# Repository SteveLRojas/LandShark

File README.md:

# LandShark
FPGA board for motor control applications. Compatible with the Alchemy board.

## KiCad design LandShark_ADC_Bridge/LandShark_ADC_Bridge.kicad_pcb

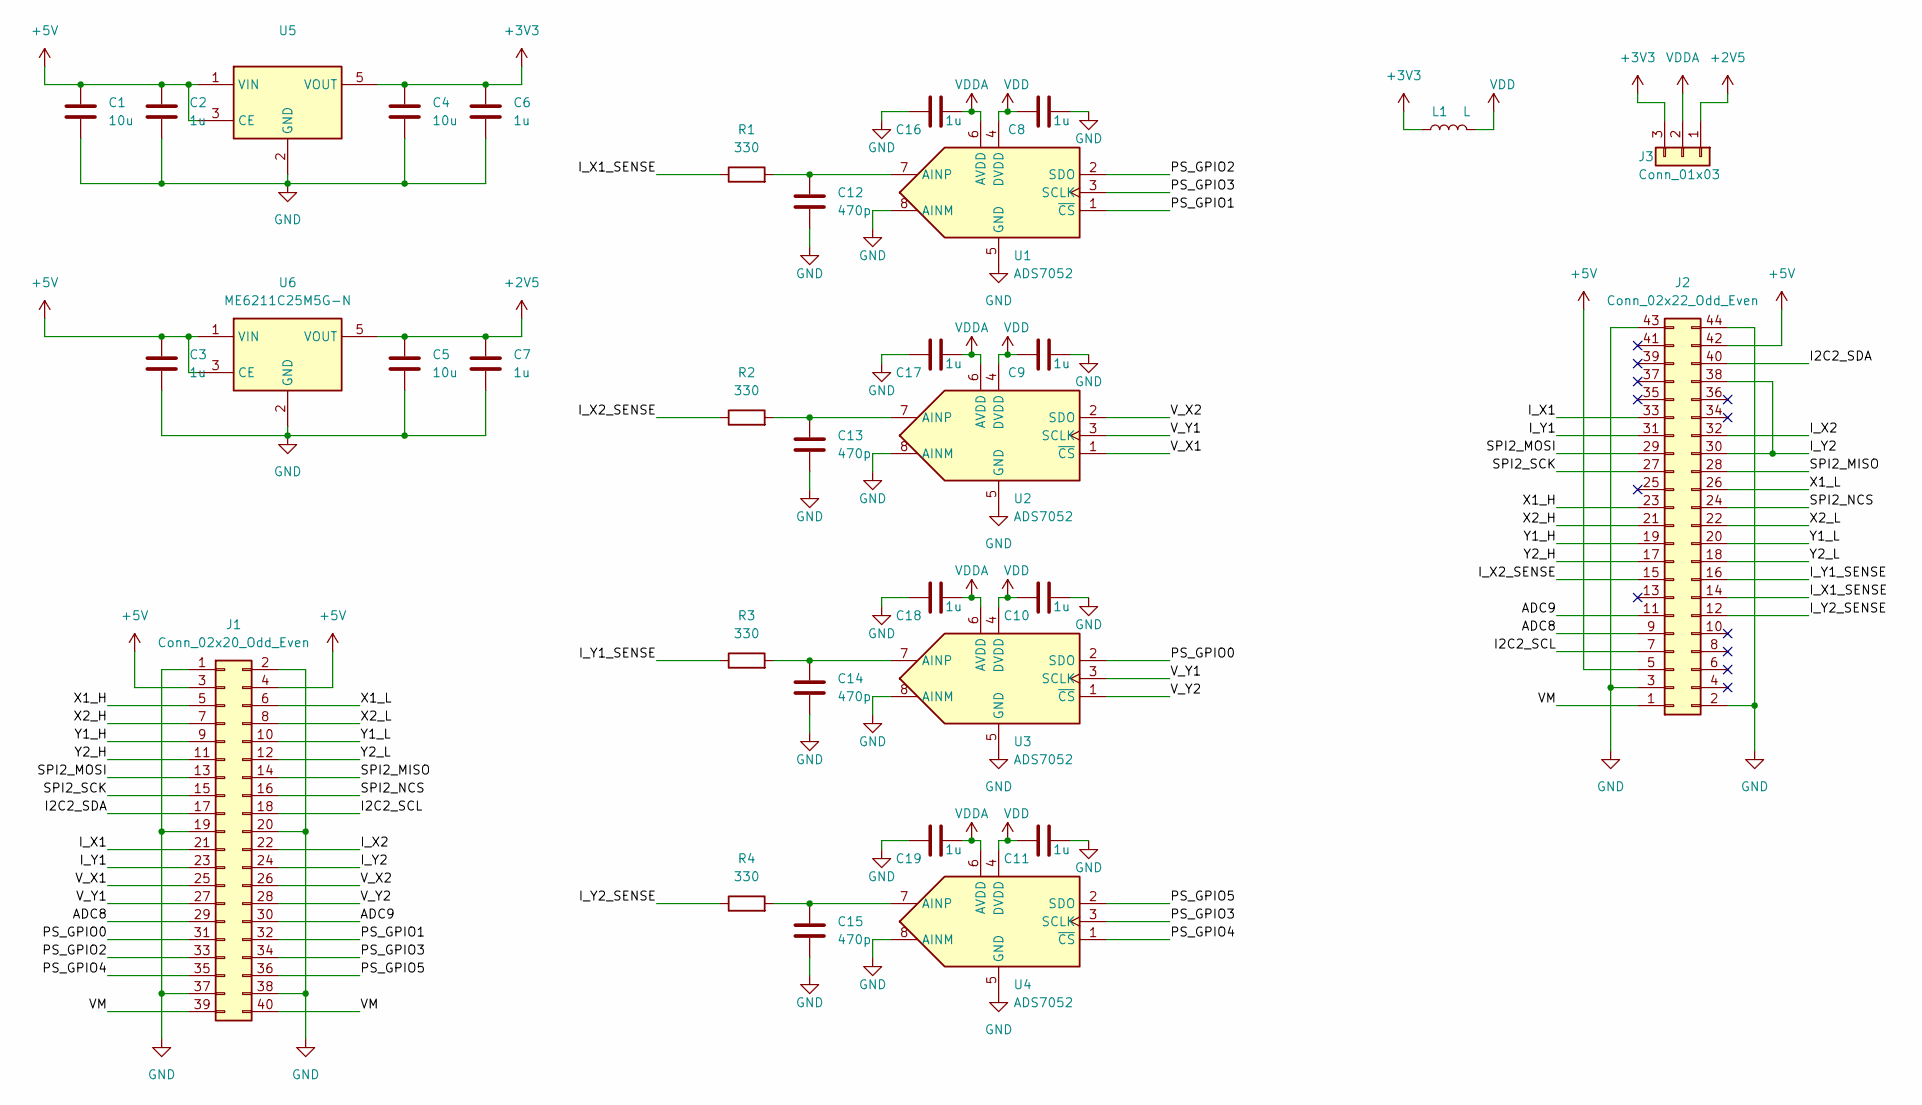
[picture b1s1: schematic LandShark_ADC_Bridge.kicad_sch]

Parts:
C1, C4, C5: 10u; C_1206_3216Metric
C2, C3, C6, C7, C8, C9, C10, C11, C16, C17, C18, C19: 1u; C_0805_2012Metric
C12, C13, C14, C15: 470p; C_0603_1608Metric
J1: Conn_02x20_Odd_Even; con_Alchemy_mirrored
J2: Conn_02x22_Odd_Even; PinHeader_2x22_P2.54mm_Vertical
J3: Conn_01x03; PinHeader_1x03_P1.27mm_Vertical
L1: L; L_0805_2012Metric
R1, R2, R3, R4: 330; R_0603_1608Metric
U1, U2, U3, U4: ADS7052; ADS7052IRUGR
U5: XC6219B332MR; SOT-23-5
U6: ME6211C25M5G-N; SOT-23-5

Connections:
+2V5: C5.1, C7.1, J3.1, U6.5 (VOUT)
+3V3: C4.1, C6.1, J3.3, L1.1, U5.5 (VOUT)
+5V: C1.1, C2.1, C3.1, J1.3, J1.4, J2.5, J2.42, U5.1 (VIN), U5.3 (CE), U6.1 (VIN), U6.3 (CE)
/ADC8: J1.29, J2.9
/ADC9: J1.30, J2.11
/I2C2_SCL: J1.18, J2.7
/I2C2_SDA: J1.17, J2.40
/I_X1: J1.21, J2.33
/I_X1_SENSE: J2.14, R1.1
/I_X2: J1.22, J2.32
/I_X2_SENSE: J2.15, R2.1
/I_Y1: J1.23, J2.31
/I_Y1_SENSE: J2.16, R3.1
/I_Y2: J1.24, J2.30, J2.38
/I_Y2_SENSE: J2.12, R4.1
/PS_GPIO0: J1.31, U3.2 (SDO)
/PS_GPIO1: J1.32, U1.1 (~CS)
/PS_GPIO2: J1.33, U1.2 (SDO)
/PS_GPIO3: J1.34, U1.3 (SCLK), U4.3 (SCLK)
/PS_GPIO4: J1.35, U4.1 (~CS)
/PS_GPIO5: J1.36, U4.2 (SDO)
/SPI2_MISO: J1.14, J2.28
/SPI2_MOSI: J1.13, J2.29
/SPI2_NCS: J1.16, J2.24
/SPI2_SCK: J1.15, J2.27
/VM: J1.39, J1.40, J2.1
/V_X1: J1.25, U2.1 (~CS)
/V_X2: J1.26, U2.2 (SDO)
/V_Y1: J1.27, U2.3 (SCLK), U3.3 (SCLK)
/V_Y2: J1.28, U3.1 (~CS)
/X1_H: J1.5, J2.23
/X1_L: J1.6, J2.26
/X2_H: J1.7, J2.21
/X2_L: J1.8, J2.22
/Y1_H: J1.9, J2.19
/Y1_L: J1.10, J2.20
/Y2_H: J1.11, J2.17
/Y2_L: J1.12, J2.18
GND: C1.2, C2.2, C3.2, C4.2, C5.2, C6.2, C7.2, C8.2, C9.2, C10.2, C11.2, C12.1, C13.1, C14.1, C15.1, C16.1, C17.1, C18.1, C19.1, J1.1, J1.2, J1.19, J1.20, J1.37, J1.38, J2.2, J2.3, J2.43, J2.44, U1.5 (GND), U1.8 (AINM), U2.5 (GND), U2.8 (AINM), U3.5 (GND), U3.8 (AINM), U4.5 (GND), U4.8 (AINM), U5.2 (GND), U6.2 (GND)
unnamed: C12.2, R1.2, U1.7 (AINP)
unnamed: C13.2, R2.2, U2.7 (AINP)
unnamed: C14.2, R3.2, U3.7 (AINP)
unnamed: C15.2, R4.2, U4.7 (AINP)
VDD: C8.1, C9.1, C10.1, C11.1, L1.2, U1.4 (DVDD), U2.4 (DVDD), U3.4 (DVDD), U4.4 (DVDD)
VDDA: C16.2, C17.2, C18.2, C19.2, J3.2, U1.6 (AVDD), U2.6 (AVDD), U3.6 (AVDD), U4.6 (AVDD)

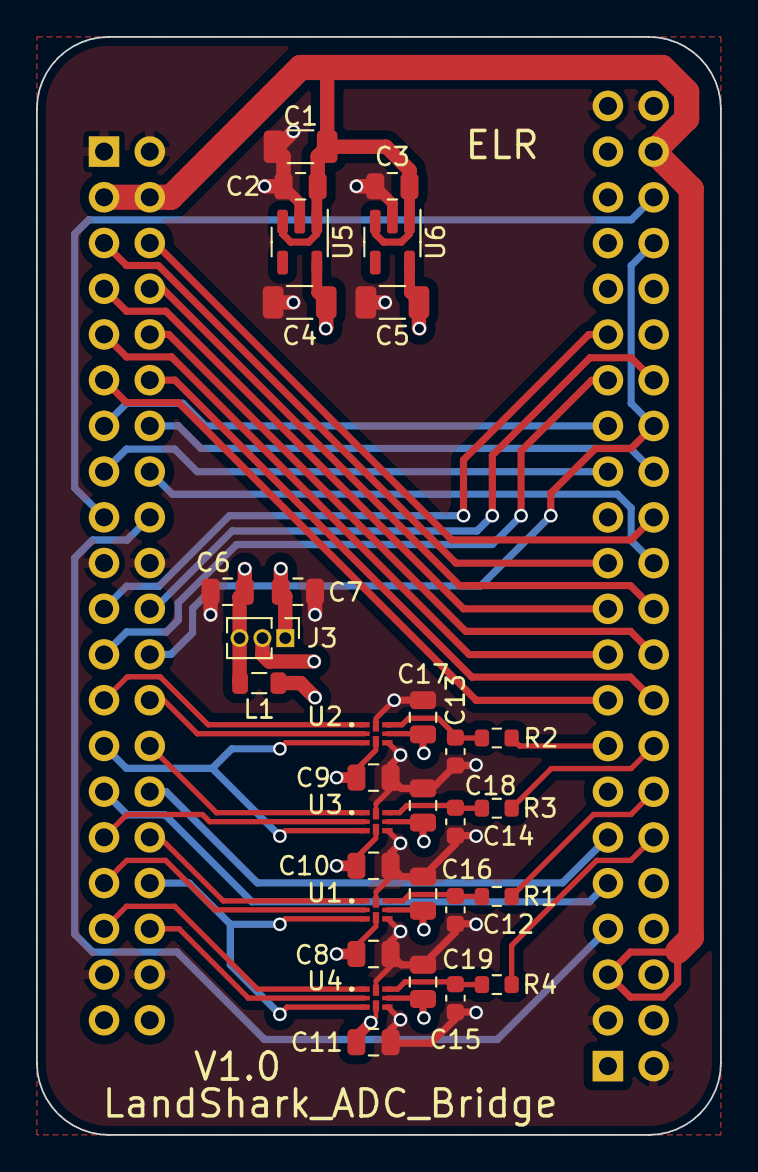
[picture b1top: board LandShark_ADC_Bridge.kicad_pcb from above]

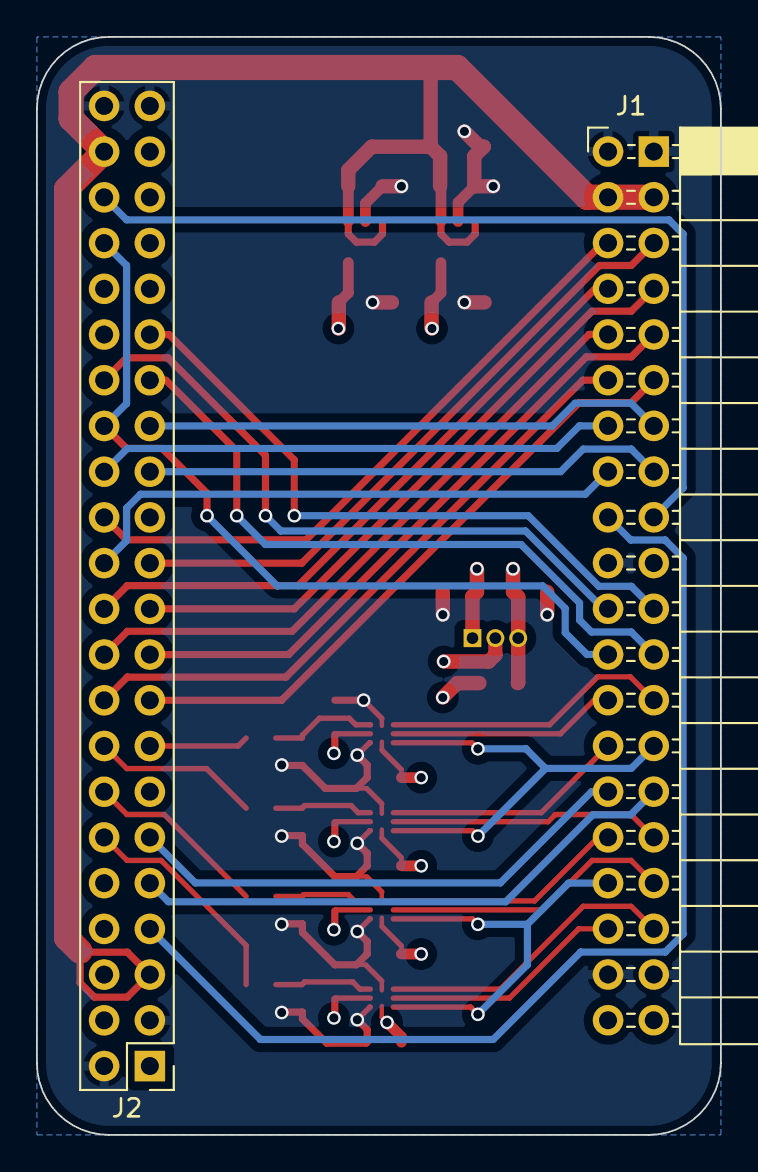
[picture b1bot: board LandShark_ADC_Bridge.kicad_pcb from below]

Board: 4 copper layers, 38.0 x 61.0 mm, 33 parts (2 on the bottom side), 45 nets.

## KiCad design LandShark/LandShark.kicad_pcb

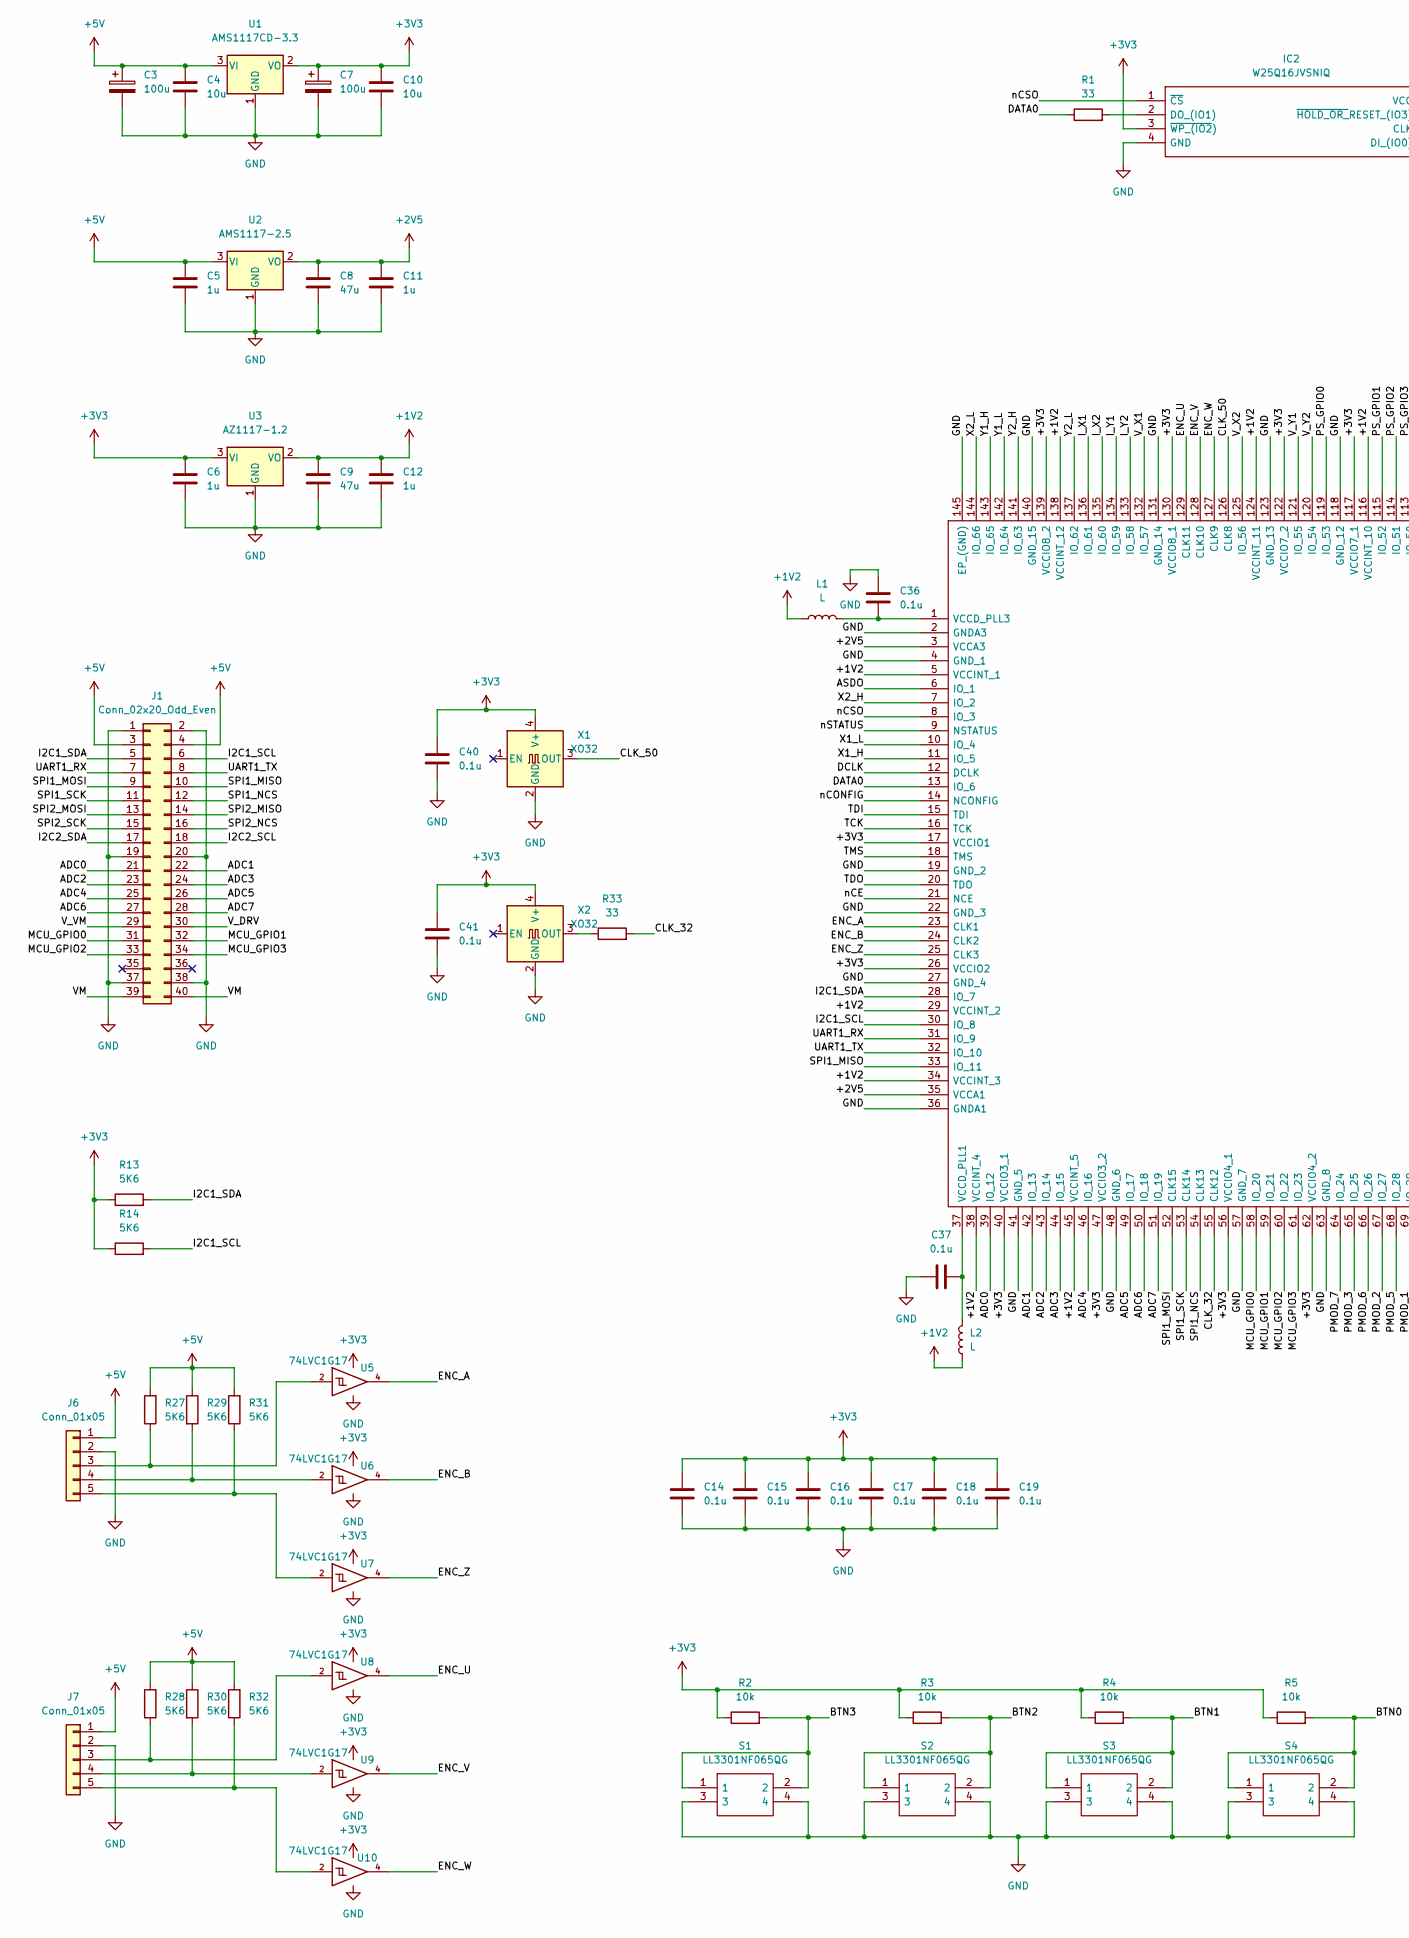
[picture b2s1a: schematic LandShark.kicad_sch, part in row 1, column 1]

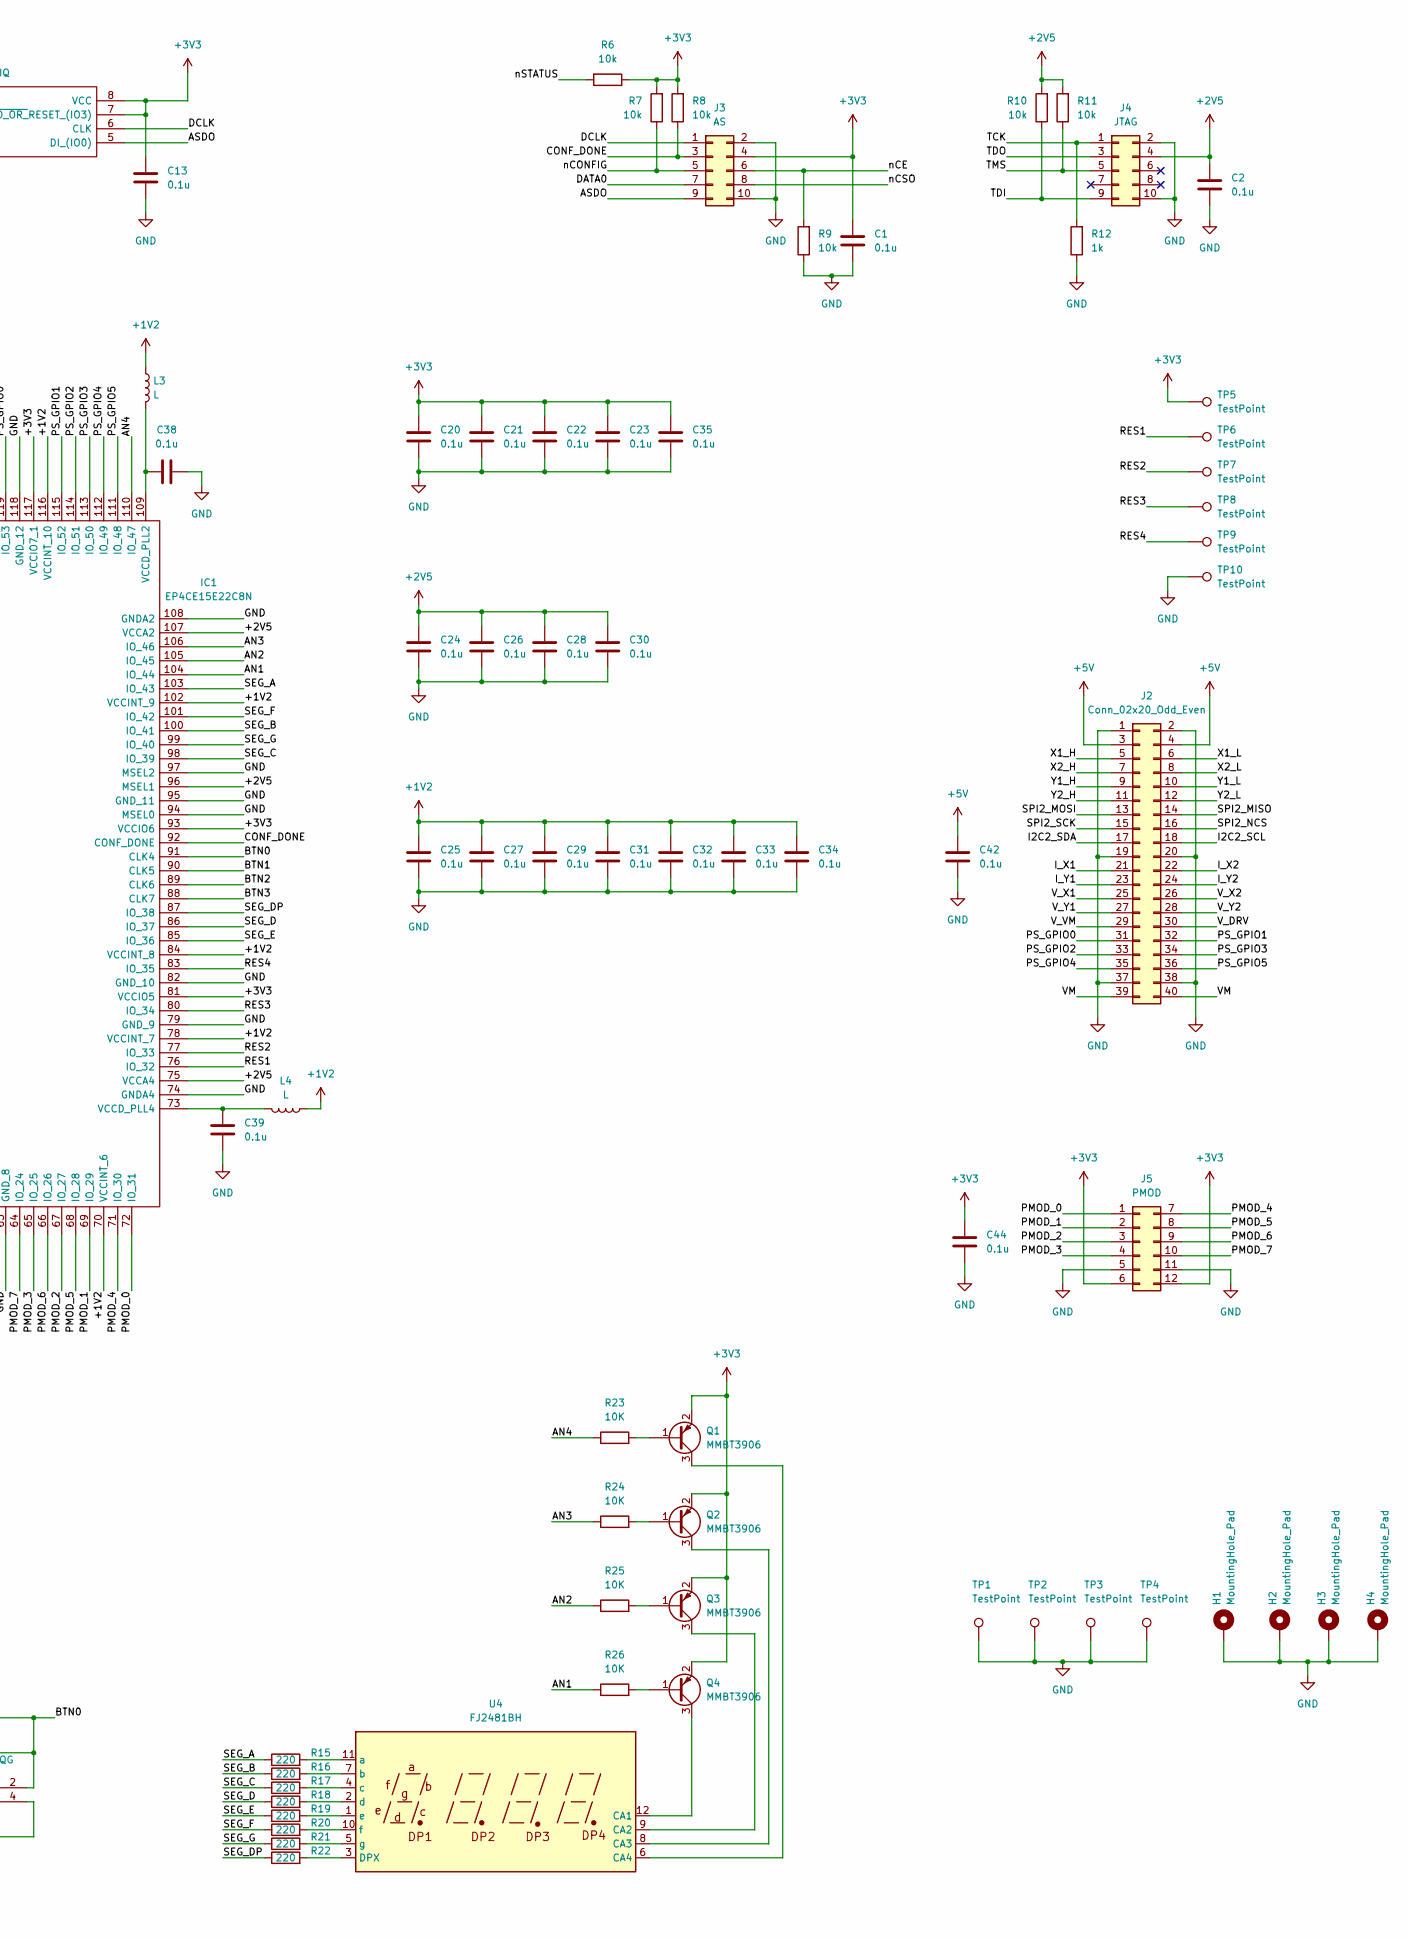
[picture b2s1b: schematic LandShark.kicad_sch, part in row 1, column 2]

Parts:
C1, C2, C13, C14, C15, C16, C17, C18, C19, C20, C21, C22, C23, C24, C25, C26, C27, C28, C29, C30, C31, C32, C33, C34, C35, C36, C37, C38, C39, C40, C41, C42, C44: 0.1u; C_0805_2012Metric
C3, C7: 100u; CP_Elec_6.3x5.2
C4, C10: 10u; C_1206_3216Metric
C5, C6, C11, C12: 1u; C_0805_2012Metric
C8, C9: 47u; C_1206_3216Metric
H1, H2, H3, H4: MountingHole_Pad; MountingHole_3.2mm_M3_Pad
IC1: EP4CE15E22C8N; QFP50P2200X2200X165-145N; Mouser Part Number 989-EP4CE15E22C8N
IC2: W25Q16JVSNIQ; SOIC127P600X175-8N; Manufacturer_Part_Number W25Q16JVSNIQ; Mouser Part Number 454-W25Q16JVSNIQ
J1: Conn_02x20_Odd_Even; PinSocket_2x20_P2.54mm_Horizontal
J2: Conn_02x20_Odd_Even; PinHeader_2x20_P2.54mm_Horizontal
J3: AS; IDC-Header_2x05_P2.54mm_Vertical
J4: JTAG; IDC-Header_2x05_P2.54mm_Vertical
J5: PMOD; pmod_socket_6x2
J6, J7: Conn_01x05; PinHeader_1x05_P2.54mm_Vertical
L1, L2, L3, L4: L; L_0805_2012Metric
Q1, Q2, Q3, Q4: MMBT3906; SOT-23
R1, R33: 33; R_0805_2012Metric
R2, R3, R4, R5, R6, R7, R8, R9, R10, R11: 10k; R_0805_2012Metric
R12: 1k; R_0805_2012Metric
R13, R14, R27, R28, R29, R30, R31, R32: 5K6; R_0805_2012Metric
R15, R16, R17, R18, R19, R20, R21, R22: 220; R_0805_2012Metric
R23, R24, R25, R26: 10K; R_0805_2012Metric
S1, S2, S3, S4: LL3301NF065QG; Mouser Part Number 612-LL3301NF065QG
TP1, TP2, TP3, TP4: TestPoint; TestPoint_Loop_D2.50mm_Drill1.0mm
TP5, TP6, TP7, TP8, TP9, TP10: TestPoint; TestPoint_Pad_1.5x1.5mm
U1: AMS1117CD-3.3; TO-252-3_TabPin2
U2: AMS1117-2.5; SOT-223-3_TabPin2
U3: AZ1117-1.2; SOT-223-3_TabPin2
U4: FJ2481BH
U5, U6, U7, U8, U9, U10: 74LVC1G17; SOT-353_SC-70-5
X1, X2: XO32; Oscillator_SMD_EuroQuartz_XO32-4Pin_3.2x2.5mm

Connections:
+1V2: C9.1, C12.1, C25.1, C27.1, C29.1, C31.1, C32.1, C33.1, C34.1, IC1.5 (VCCINT_1), IC1.29 (VCCINT_2), IC1.34 (VCCINT_3), IC1.38 (VCCINT_4), IC1.45 (VCCINT_5), IC1.70 (VCCINT_6), IC1.78 (VCCINT_7), IC1.84 (VCCINT_8), IC1.102 (VCCINT_9), IC1.116 (VCCINT_10), IC1.124 (VCCINT_11), IC1.138 (VCCINT_12), L1.1, L2.1, L3.1, L4.1, U3.2 (VO)
+2V5: C2.1, C8.1, C11.1, C24.1, C26.1, C28.1, C30.1, IC1.3 (VCCA3), IC1.35 (VCCA1), IC1.75 (VCCA4), IC1.96 (MSEL1), IC1.107 (VCCA2), J4.4, R10.2, R11.2, U2.2 (VO)
+3V3: C1.1, C6.1, C7.1, C10.1, C13.1, C14.1, C15.1, C16.1, C17.1, C18.1, C19.1, C20.1, C21.1, C22.1, C23.1, C35.1, C40.1, C41.1, C44.1, IC1.17 (VCCIO1), IC1.26 (VCCIO2), IC1.40 (VCCIO3_1), IC1.47 (VCCIO3_2), IC1.56 (VCCIO4_1), IC1.62 (VCCIO4_2), IC1.81 (VCCIO5), IC1.93 (VCCIO6), IC1.117 (VCCIO7_1), IC1.122 (VCCIO7_2), IC1.130 (VCCIO8_1), IC1.139 (VCCIO8_2), IC2.3 (~WP_(IO2)), IC2.7 (~HOLD_OR_RESET_(IO3)), IC2.8 (VCC), J3.4, J5.6, J5.12, Q1.2 (E), Q2.2 (E), Q3.2 (E), Q4.2 (E), R2.1, R3.1, R4.1, R5.1, R6.1, R7.2, R8.2, R13.1, R14.1, TP5.1, U1.2 (VO), U3.3 (VI), U5.5 (VCC), U6.5 (VCC), U7.5 (VCC), U8.5 (VCC), U9.5 (VCC), U10.5 (VCC), X1.4 (V+), X2.4 (V+)
+5V: C3.1, C4.1, C5.1, C42.1, J1.3, J1.4, J2.3, J2.4, J6.1, J7.1, R27.2, R28.2, R29.1, R30.1, R31.2, R32.2, U1.3 (VI), U2.3 (VI)
/ADC0: IC1.39 (IO_12), J1.21
/ADC1: IC1.42 (IO_13), J1.22
/ADC2: IC1.43 (IO_14), J1.23
/ADC3: IC1.44 (IO_15), J1.24
/ADC4: IC1.46 (IO_16), J1.25
/ADC5: IC1.49 (IO_17), J1.26
/ADC6: IC1.50 (IO_18), J1.27
/ADC7: IC1.51 (IO_19), J1.28
/AN1: IC1.104 (IO_44), R26.1
/AN2: IC1.105 (IO_45), R25.1
/AN3: IC1.106 (IO_46), R24.1
/AN4: IC1.110 (IO_47), R23.1
/ASDO: IC1.6 (IO_1), IC2.5 (DI_(IO0)), J3.9
/BTN0: IC1.91 (CLK4), R5.2, S4.1, S4.2
/BTN1: IC1.90 (CLK5), R4.2, S3.1, S3.2
/BTN2: IC1.89 (CLK6), R3.2, S2.1, S2.2
/BTN3: IC1.88 (CLK7), R2.2, S1.1, S1.2
/CLK_32: IC1.55 (CLK12), R33.2
/CLK_50: IC1.126 (CLK8), X1.3 (OUT)
/CONF_DONE: IC1.92 (CONF_DONE), J3.3, R8.1
/DATA0: IC1.13 (IO_6), J3.7, R1.1
/DCLK: IC1.12 (DCLK), IC2.6 (CLK), J3.1
/ENC_A: IC1.23 (CLK1), U5.4
/ENC_B: IC1.24 (CLK2), U6.4
/ENC_U: IC1.129 (CLK11), U8.4
/ENC_V: IC1.128 (CLK10), U9.4
/ENC_W: IC1.127 (CLK9), U10.4
/ENC_Z: IC1.25 (CLK3), U7.4
/I2C1_SCL: IC1.30 (IO_8), J1.6, R14.2
/I2C1_SDA: IC1.28 (IO_7), J1.5, R13.2
/I2C2_SCL: J1.18, J2.18
/I2C2_SDA: J1.17, J2.17
/I_X1: IC1.136 (IO_61), J2.21
/I_X2: IC1.135 (IO_60), J2.22
/I_Y1: IC1.134 (IO_59), J2.23
/I_Y2: IC1.133 (IO_58), J2.24
/MCU_GPIO0: IC1.58 (IO_20), J1.31
/MCU_GPIO1: IC1.59 (IO_21), J1.32
/MCU_GPIO2: IC1.60 (IO_22), J1.33
/MCU_GPIO3: IC1.61 (IO_23), J1.34
/PMOD_0: IC1.72 (IO_31), J5.1
/PMOD_1: IC1.69 (IO_29), J5.2
/PMOD_2: IC1.67 (IO_27), J5.3
/PMOD_3: IC1.65 (IO_25), J5.4
/PMOD_4: IC1.71 (IO_30), J5.7
/PMOD_5: IC1.68 (IO_28), J5.8
/PMOD_6: IC1.66 (IO_26), J5.9
/PMOD_7: IC1.64 (IO_24), J5.10
/PS_GPIO0: IC1.119 (IO_53), J2.31
/PS_GPIO1: IC1.115 (IO_52), J2.32
/PS_GPIO2: IC1.114 (IO_51), J2.33
/PS_GPIO3: IC1.113 (IO_50), J2.34
/PS_GPIO4: IC1.112 (IO_49), J2.35
/PS_GPIO5: IC1.111 (IO_48), J2.36
/RES1: IC1.76 (IO_32), TP6.1
/RES2: IC1.77 (IO_33), TP7.1
/RES3: IC1.80 (IO_34), TP8.1
/RES4: IC1.83 (IO_35), TP9.1
/SEG_A: IC1.103 (IO_43), R15.1
/SEG_B: IC1.100 (IO_41), R16.1
/SEG_C: IC1.98 (IO_39), R17.1
/SEG_D: IC1.86 (IO_37), R18.1
/SEG_DP: IC1.87 (IO_38), R22.1
/SEG_E: IC1.85 (IO_36), R19.1
/SEG_F: IC1.101 (IO_42), R20.1
/SEG_G: IC1.99 (IO_40), R21.1
/SPI1_MISO: IC1.33 (IO_11), J1.10
/SPI1_MOSI: IC1.52 (CLK15), J1.9
/SPI1_NCS: IC1.54 (CLK13), J1.12
/SPI1_SCK: IC1.53 (CLK14), J1.11
/SPI2_MISO: J1.14, J2.14
/SPI2_MOSI: J1.13, J2.13
/SPI2_NCS: J1.16, J2.16
/SPI2_SCK: J1.15, J2.15
/TCK: IC1.16 (TCK), J4.1, R12.2
/TDI: IC1.15 (TDI), J4.9, R10.1
/TDO: IC1.20 (TDO), J4.3
/TMS: IC1.18 (TMS), J4.5, R11.1
/UART1_RX: IC1.31 (IO_9), J1.7
/UART1_TX: IC1.32 (IO_10), J1.8
/VM: J1.39, J1.40, J2.39, J2.40
/V_DRV: J1.30, J2.30
/V_VM: J1.29, J2.29
/V_X1: IC1.132 (IO_57), J2.25
/V_X2: IC1.125 (IO_56), J2.26
/V_Y1: IC1.121 (IO_55), J2.27
/V_Y2: IC1.120 (IO_54), J2.28
/X1_H: IC1.11 (IO_5), J2.5
/X1_L: IC1.10 (IO_4), J2.6
/X2_H: IC1.7 (IO_2), J2.7
/X2_L: IC1.144 (IO_66), J2.8
/Y1_H: IC1.143 (IO_65), J2.9
/Y1_L: IC1.142 (IO_64), J2.10
/Y2_H: IC1.141 (IO_63), J2.11
/Y2_L: IC1.137 (IO_62), J2.12
/nCE: IC1.21 (NCE), J3.6, R9.2
/nCONFIG: IC1.14 (NCONFIG), J3.5, R7.1
/nCSO: IC1.8 (IO_3), IC2.1 (~CS), J3.8
/nSTATUS: IC1.9 (NSTATUS), R6.2
GND: C1.2, C2.2, C3.2, C4.2, C5.2, C6.2, C7.2, C8.2, C9.2, C10.2, C11.2, C12.2, C13.2, C14.2, C15.2, C16.2, C17.2, C18.2, C19.2, C20.2, C21.2, C22.2, C23.2, C24.2, C25.2, C26.2, C27.2, C28.2, C29.2, C30.2, C31.2, C32.2, C33.2, C34.2, C35.2, C36.2, C37.2, C38.2, C39.1, C40.2, C41.2, C42.2, C44.2, H1.1, H2.1, H3.1, H4.1, IC1.2 (GNDA3), IC1.4 (GND_1), IC1.19 (GND_2), IC1.22 (GND_3), IC1.27 (GND_4), IC1.36 (GNDA1), IC1.41 (GND_5), IC1.48 (GND_6), IC1.57 (GND_7), IC1.63 (GND_8), IC1.74 (GNDA4), IC1.79 (GND_9), IC1.82 (GND_10), IC1.94 (MSEL0), IC1.95 (GND_11), IC1.97 (MSEL2), IC1.108 (GNDA2), IC1.118 (GND_12), IC1.123 (GND_13), IC1.131 (GND_14), IC1.140 (GND_15), IC1.145 (EP_(GND)), IC2.4 (GND), J1.1, J1.2, J1.19, J1.20, J1.37, J1.38, J2.1, J2.2, J2.19, J2.20, J2.37, J2.38, J3.2, J3.10, J4.2, J4.10, J5.5, J5.11, J6.2, J7.2, R9.1, R12.1, S1.3, S1.4, S2.3, S2.4, S3.3, S3.4, S4.3, S4.4, TP1.1, TP2.1, TP3.1, TP4.1, TP10.1, U1.1 (GND), U2.1 (GND), U3.1 (GND), U5.3 (GND), U6.3 (GND), U7.3 (GND), U8.3 (GND), U9.3 (GND), U10.3 (GND), X1.2 (GND), X2.2 (GND)
unnamed: C36.1, IC1.1 (VCCD_PLL3), L1.2
unnamed: C37.1, IC1.37 (VCCD_PLL1), L2.2
unnamed: C39.2, IC1.73 (VCCD_PLL4), L4.2
unnamed: C38.1, IC1.109 (VCCD_PLL2), L3.2
unnamed: IC2.2 (DO_(IO1)), R1.2
unnamed: J6.3, R27.1, U5.2
unnamed: J6.4, R29.2, U6.2
unnamed: J6.5, R31.1, U7.2
unnamed: J7.3, R28.1, U8.2
unnamed: J7.4, R30.2, U9.2
unnamed: J7.5, R32.1, U10.2
unnamed: Q1.1 (B), R23.2
unnamed: Q1.3 (C), U4.6 (CA4)
unnamed: Q2.1 (B), R24.2
unnamed: Q2.3 (C), U4.8 (CA3)
unnamed: Q3.1 (B), R25.2
unnamed: Q3.3 (C), U4.9 (CA2)
unnamed: Q4.1 (B), R26.2
unnamed: Q4.3 (C), U4.12 (CA1)
unnamed: R15.2, U4.11 (a)
unnamed: R16.2, U4.7 (b)
unnamed: R17.2, U4.4 (c)
unnamed: R18.2, U4.2 (d)
unnamed: R19.2, U4.1 (e)
unnamed: R20.2, U4.10 (f)
unnamed: R21.2, U4.5 (g)
unnamed: R22.2, U4.3 (DPX)
unnamed: R33.1, X2.3 (OUT)

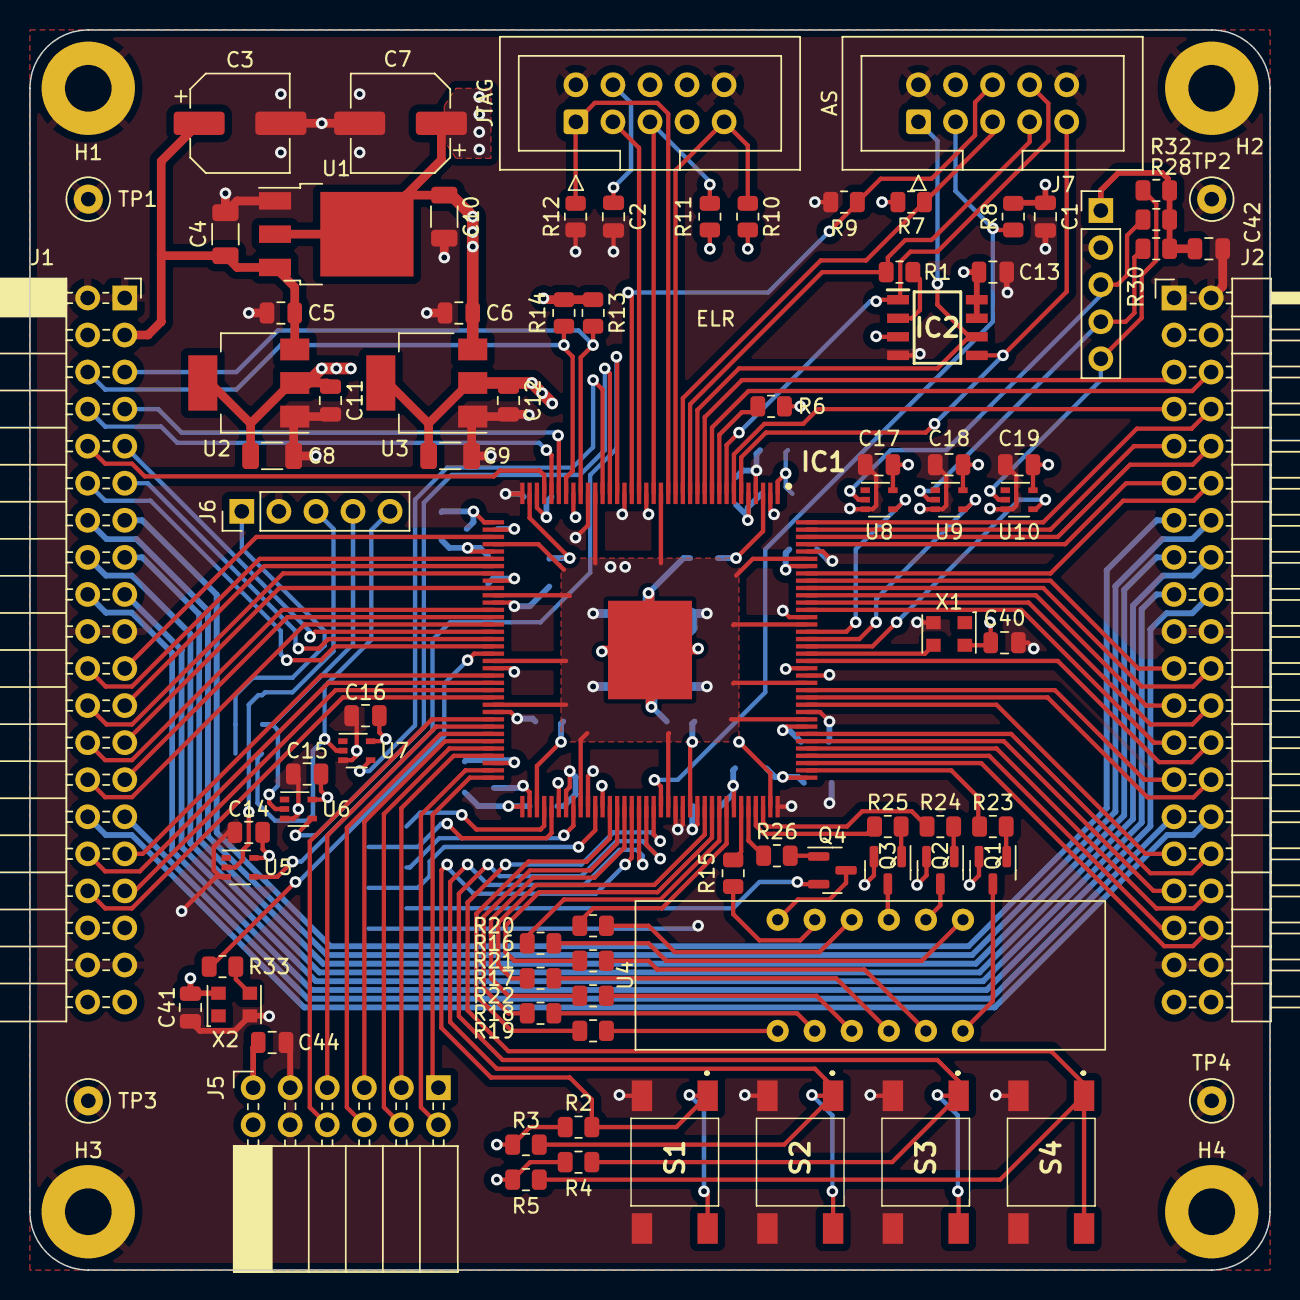
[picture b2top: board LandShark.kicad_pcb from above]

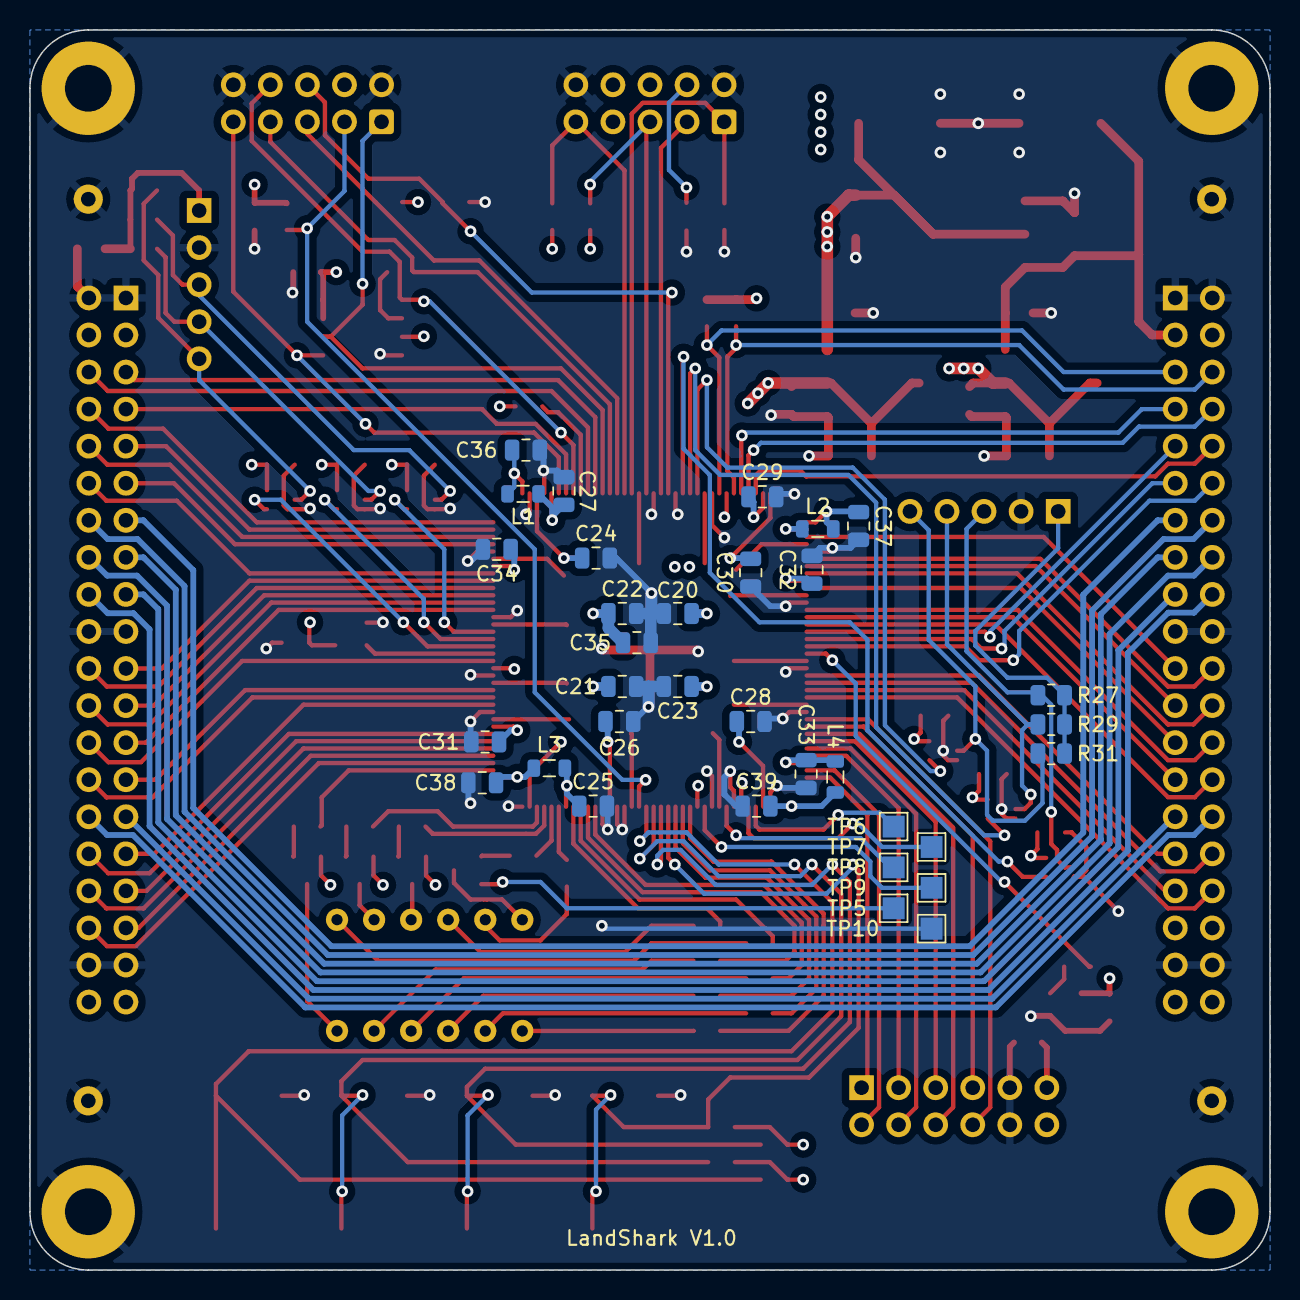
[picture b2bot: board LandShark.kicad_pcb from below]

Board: 4 copper layers, 85.0 x 85.0 mm, 123 parts (33 on the bottom side), 132 nets.

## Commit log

2025-06-05 Added design files
2026-02-09 Added LandShark_ADC_Bridge
